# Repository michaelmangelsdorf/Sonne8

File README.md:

UPDATE: There is now a [successor project](https://github.com/michaelmangelsdorf/myth).

Computer project around an 8-bit microcontroller I've designed.

There are design files for a working single-board computer built around it in the 'Prototype' folder. I've had the PCB for it manufactured by JLCPCB during various revisions. The computer now works fine at 8 MHz system clock, which corresponds to around 1 million instructions per second. The main components are all 74HC-series CMOS chips. I basically wanted to design a CPU I could actually build from parts, not just inside an FPGA like [my previous](https://github.com/Dosflange/Paver) 16-bit machine.

The current reference schematics I'm using are [here](https://github.com/Dosflange/Myth/blob/main/docs/static/myth.pdf).
If I were to build another board, it would probably be based on the KiCad files in the 'Schematics' folder, where I
separated the schematics into functional modules.

So what this image shows is not an application board with an Arduino or anything, it is the actual microcontroller. The current version
has exactly 100 chips.

There are two software emulators I've written for this system. The code is very small, hopefully it's a good reference for finding out about the CPU.
The decoder-based [implementation](https://github.com/Dosflange/Myth/blob/main/Dev/src/clox/myth.h) is more high-level, and
the [dispatch table](https://github.com/Dosflange/Myth/blob/main/Dev/src/clox/vtable.c) version better suited to finding out about particular instructions.

[Documentation WIP](https://michaelmangelsdorf.github.io/Sonne8/)

__Update Sep.24__:

I've written a new assembler for this machine in Go(lang). The first thing I ported from the old format was
this multiplication routine. It multiplies two unsigned 8-bit numbers and returns a 16-bit result.
You can try it out with the tools in the 'Dev' folder.

```
Goldie/LOX assembly log
Page.Offset  Object code  Lid Line# Source text

                        048 0062  ;****** ***************************************************************
                        048 0063  P[Mul8]+  (Multiplies R by O, result in R and O)
                        048 0064  ;****** ***************************************************************
                        048 0065  
21.00:  07 5E           043 0066        OWN i6        (Save return pointer in L7/L6)
21.02:  79              043 0067        o1            (Multiplicand into L1, turns into low order result)
21.03:  68              043 0068        r0            (Multiplier into L0)
21.04:  10 6A           043 0069        CLR r2        (Clear high-order result, copy to L2)
21.06:  85 07           043 0070        ni 07h        (Initialise loop counter, 8 bits)
                        043 0071  
                        043 0072      O[Mul8Loop]
                        043 0073   
21.08:  80 01           043 0074        no 01h        (Bit mask for LSB)
21.0A:  61 18           043 0075        1r AND        (Check if multiplicand has LSB set)
21.0C:  8E 12           043 0076        nf >Mul8Skip  (Skip if not)
21.0E:  60 72 1B 6A     043 0077        0r 2o ADD r2  (Add multiplier to high order result)
                        043 0078  
                        043 0079      O[Mul8Skip]
                        043 0080  
21.12:  80 01           043 0081        no 01h        (Bit mask for LSB)
21.14:  62 18 6B        043 0082        2r AND r3     (Prepare flag of whether high order LSB is set)
21.17:  61 16 69        043 0083        1r SRR r1      (Shift low-order result right)
21.1A:  62 16 6A        043 0084        2r SRR r2       (Shift high-order result right)
                        043 0085  
21.1D:  63 8E 25        043 0086        3r nf >Mul8Done  (Check flag from earlier - HO LSB set?)
21.20:  84 80           043 0087        nr 80h          (Bit mask for MSB)
21.22:  71 19 69        043 0088        1o IOR r1     (Handle shift-result carry bit into MSB)
                        043 0089  
                        043 0090      O[Mul8Done]
                        043 0091  
21.25:  8C 08           043 0092        nw <Mul8Loop
21.27:  71              043 0093        1o            (Result low-order)
21.28:  62              043 0094        2r            (Result high-order)
21.29:  56 05           043 0095        6i RET        (Restore return pointer from L7/L6)
```

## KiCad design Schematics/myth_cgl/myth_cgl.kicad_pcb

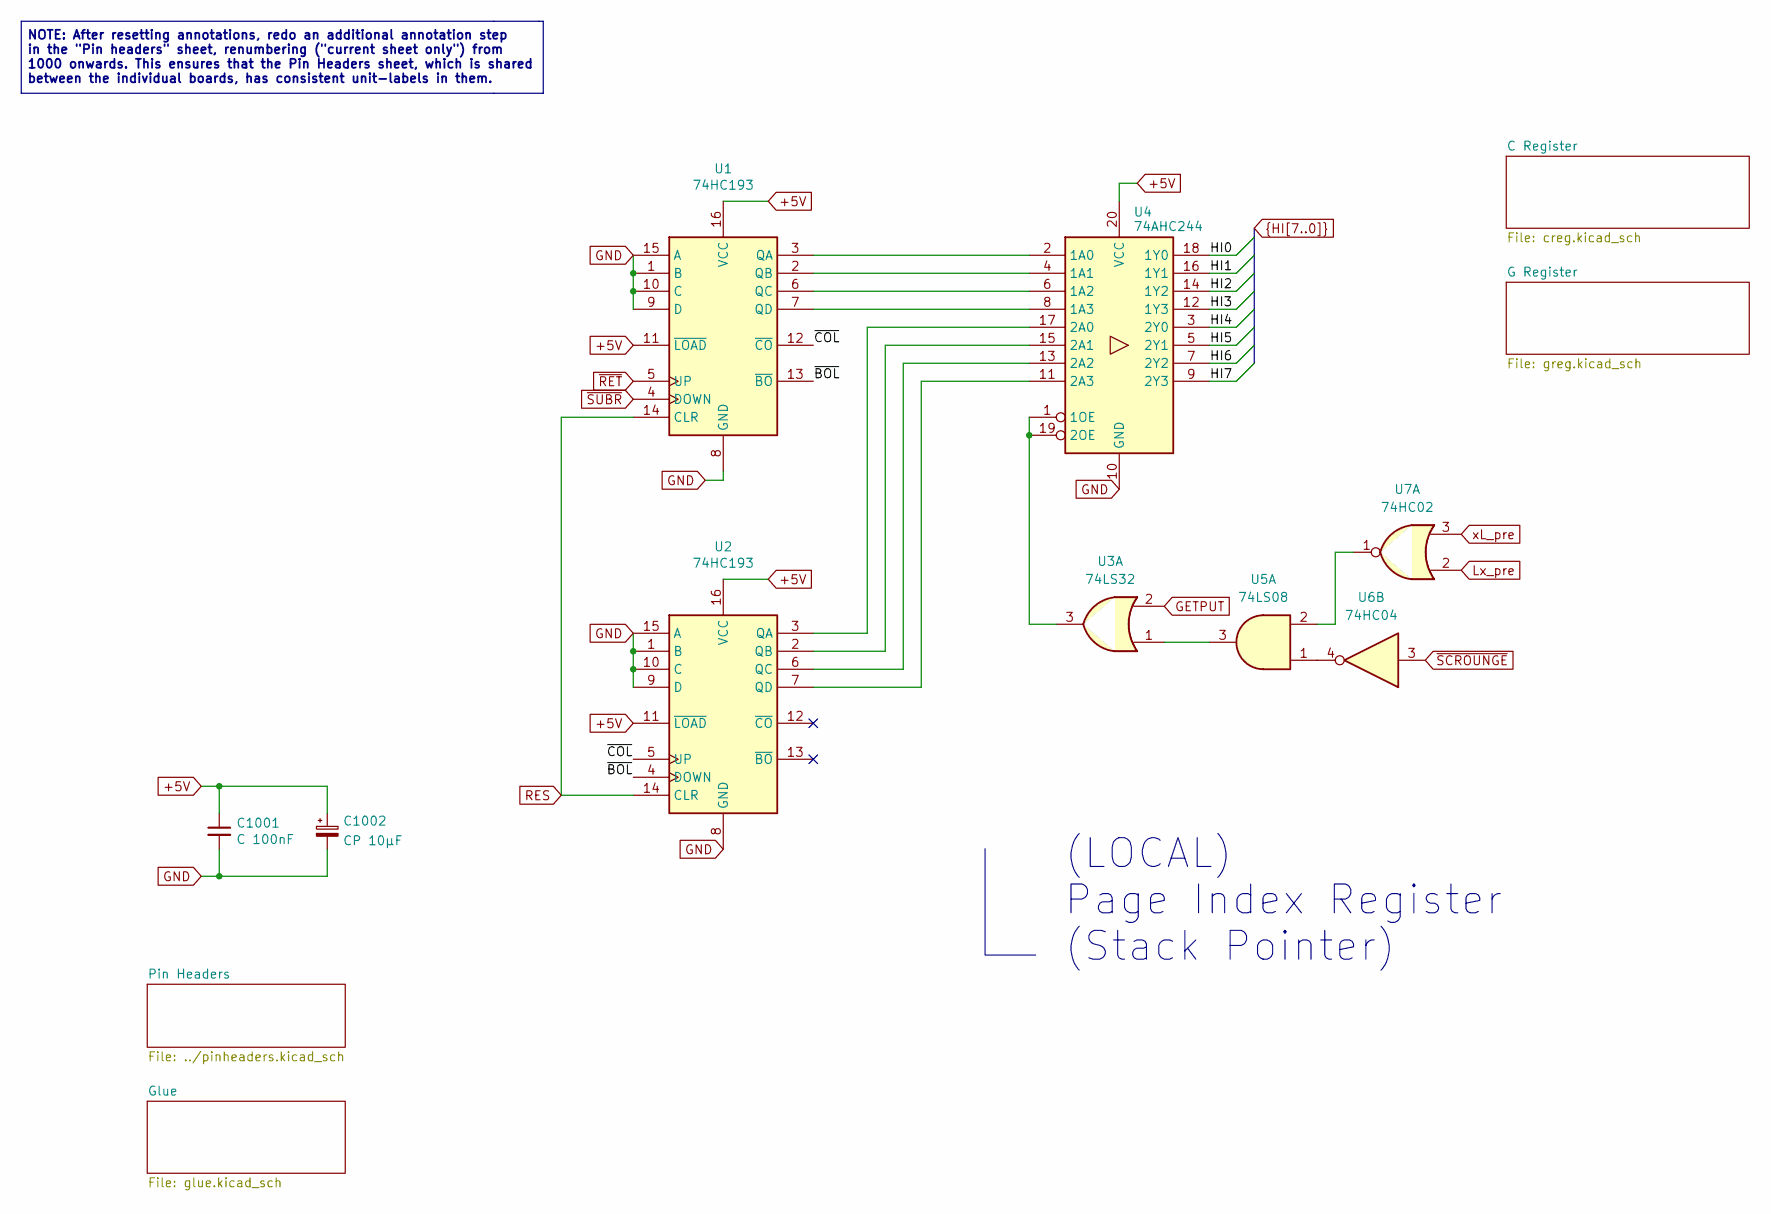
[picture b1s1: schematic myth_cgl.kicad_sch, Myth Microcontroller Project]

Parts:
C1001: C 100nF; C_Disc_D5.0mm_W2.5mm_P2.50mm
C1002: CP 10μF; CP_Radial_D6.3mm_P2.50mm
U1, U2: 74HC193; DIP-16_W7.62mm_Socket_LongPads
U3: 74LS32; DIP-14_W7.62mm_LongPads
U4: 74AHC244; DIP-20_W7.62mm_Socket_LongPads
U5: 74LS08; DIP-14_W7.62mm_LongPads
U6: 74HC04; DIP-14_W7.62mm_LongPads
U7: 74HC02; DIP-14_W7.62mm_LongPads

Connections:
+5V: C1001.1, C1002.1, U1.11 (~LOAD), U1.16 (VCC), U2.11 (~LOAD), U2.16 (VCC), U4.20 (VCC); also elsewhere on the board
/~BOL: U1.13 (~BO), U2.4 (DOWN)
/~COL: U1.12 (~CO), U2.5 (UP)
GETPUT: U3.2; also elsewhere on the board
HI0: U4.18 (1Y0); also elsewhere on the board
HI1: U4.16 (1Y1); also elsewhere on the board
HI2: U4.14 (1Y2); also elsewhere on the board
HI3: U4.12 (1Y3); also elsewhere on the board
HI4: U4.3 (2Y0); also elsewhere on the board
HI5: U4.5 (2Y1); also elsewhere on the board
HI6: U4.7 (2Y2); also elsewhere on the board
HI7: U4.9 (2Y3); also elsewhere on the board
Lx_pre: U7.2; also elsewhere on the board
unnamed: U1.3 (QA), U4.2 (1A0)
unnamed: U1.2 (QB), U4.4 (1A1)
unnamed: U1.6 (QC), U4.6 (1A2)
unnamed: U1.7 (QD), U4.8 (1A3)
unnamed: U2.3 (QA), U4.17 (2A0)
unnamed: U2.2 (QB), U4.15 (2A1)
unnamed: U2.6 (QC), U4.13 (2A2)
unnamed: U2.7 (QD), U4.11 (2A3)
unnamed: U3.1, U5.3
unnamed: U3.3, U4.1 (1OE), U4.19 (2OE)
unnamed: U5.1, U6.4
unnamed: U5.2, U7.1
RES: U1.14 (CLR), U2.14 (CLR); also elsewhere on the board
xL_pre: U7.3; also elsewhere on the board
~RET: U1.5 (UP); also elsewhere on the board
~SCROUNGE: U6.3
~SUBR: U1.4 (DOWN), U6.2; also elsewhere on the board

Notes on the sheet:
NOTE: After resetting annotations, redo an additional annotation step in the "Pin headers" sheet, renumbering ("current sheet only") from 1000 onwards. This ensures that the Pin Headers sheet, which is shared between the individual boards, has consistent unit-labels in them.
(LOCAL) Page Index Register (Stack Pointer)

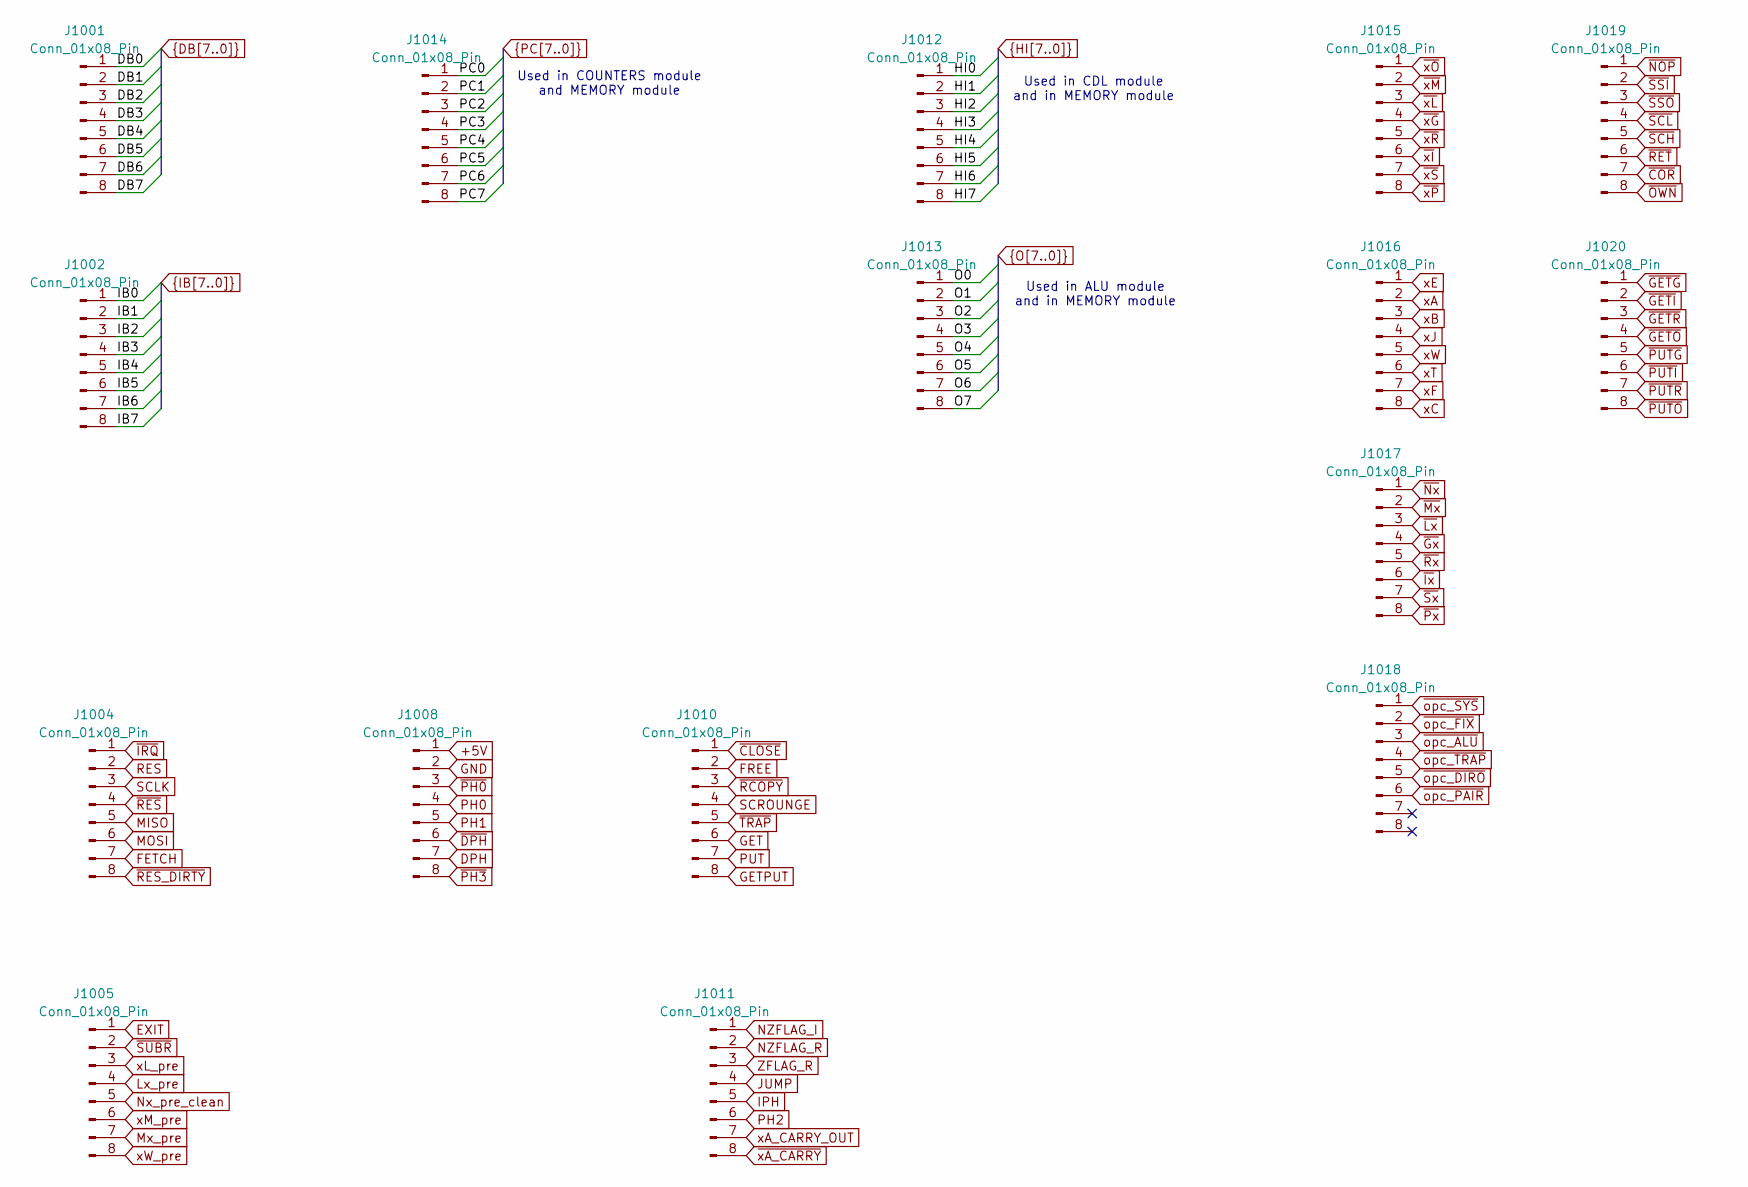
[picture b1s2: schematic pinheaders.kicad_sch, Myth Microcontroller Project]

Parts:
J1001, J1002, J1004, J1005, J1008, J1010, J1011, J1012, J1013, J1014, J1015, J1016, J1017, J1018, J1019, J1020: Conn_01x08_Pin; PinHeader_1x08_P2.54mm_Vertical

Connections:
+5V: J1008.1; also elsewhere on the board
DB0: J1001.1; also elsewhere on the board
DB1: J1001.2; also elsewhere on the board
DB2: J1001.3; also elsewhere on the board
DB3: J1001.4; also elsewhere on the board
DB4: J1001.5; also elsewhere on the board
DB5: J1001.6; also elsewhere on the board
DB6: J1001.7; also elsewhere on the board
DB7: J1001.8; also elsewhere on the board
DPH: J1008.7
EXIT: J1005.1; also elsewhere on the board
FETCH: J1004.7
FREE: J1010.2; also elsewhere on the board
GET: J1010.6
GETPUT: J1010.8; also elsewhere on the board
HI0: J1012.1; also elsewhere on the board
HI1: J1012.2; also elsewhere on the board
HI2: J1012.3; also elsewhere on the board
HI3: J1012.4; also elsewhere on the board
HI4: J1012.5; also elsewhere on the board
HI5: J1012.6; also elsewhere on the board
HI6: J1012.7; also elsewhere on the board
HI7: J1012.8; also elsewhere on the board
IB0: J1002.1
IB1: J1002.2
IB2: J1002.3
IB3: J1002.4
IB4: J1002.5
IB5: J1002.6
IB6: J1002.7
IB7: J1002.8
IPH: J1011.5; also elsewhere on the board
JUMP: J1011.4
Lx_pre: J1005.4; also elsewhere on the board
MISO: J1004.5
MOSI: J1004.6
Mx_pre: J1005.7; also elsewhere on the board
NZFLAG_I: J1011.1
NZFLAG_R: J1011.2
Nx_pre_clean: J1005.5; also elsewhere on the board
O0: J1013.1
O1: J1013.2
O2: J1013.3
O3: J1013.4
O4: J1013.5
O5: J1013.6
O6: J1013.7
O7: J1013.8
PC0: J1014.1
PC1: J1014.2
PC2: J1014.3
PC3: J1014.4
PC4: J1014.5
PC5: J1014.6
PC6: J1014.7
PC7: J1014.8
PH0: J1008.4
PH1: J1008.5
PH2: J1011.6
PUT: J1010.7
RES: J1004.2; also elsewhere on the board
SCLK: J1004.3
SCROUNGE: J1010.4
ZFLAG_R: J1011.3
xA: J1016.2
xA_CARRY_OUT: J1011.7
xB: J1016.3
xC: J1016.8; also elsewhere on the board
xE: J1016.1
xF: J1016.7
xJ: J1016.4
xL_pre: J1005.3; also elsewhere on the board
xM_pre: J1005.6; also elsewhere on the board
xT: J1016.6
xW: J1016.5
xW_pre: J1005.8
~CLOSE: J1010.1
~COR: J1019.7; also elsewhere on the board
~DPH: J1008.6
~Dx: J1017.4; also elsewhere on the board
~GETD: J1020.1
~GETI: J1020.2
~GETO: J1020.4
~GETR: J1020.3
~IRQ: J1004.1
~Ix: J1017.6
~Lx: J1017.3
~Mx: J1017.2
~NOP: J1019.1
~Nx: J1017.1
~OWN: J1019.8; also elsewhere on the board
~PH0: J1008.3; also elsewhere on the board
~PH3: J1008.8
~PUTD: J1020.5; also elsewhere on the board
~PUTI: J1020.6
~PUTO: J1020.8
~PUTR: J1020.7
~Px: J1017.8
~RCOPY: J1010.3
~RES_DIRTY: J1004.8
~RES: J1004.4; also elsewhere on the board
~RET: J1019.6; also elsewhere on the board
~Rx: J1017.5
~SCH: J1019.5
~SCL: J1019.4
~SSI: J1019.2
~SSO: J1019.3
~SUBR: J1005.2; also elsewhere on the board
~Sx: J1017.7
~TRAP: J1010.5
~opc_ALU: J1018.3
~opc_DIRO: J1018.5
~opc_FIX: J1018.2
~opc_PAIR: J1018.6
~opc_SYS: J1018.1
~opc_TRAP: J1018.4
~xA_CARRY: J1011.8; also elsewhere on the board
~xD: J1015.4
~xI: J1015.6
~xL: J1015.3
~xM: J1015.2
~xO: J1015.1
~xP: J1015.8
~xR: J1015.5
~xS: J1015.7

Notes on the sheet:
Used in COUNTERS module and MEMORY module
Used in CDL module and in MEMORY module
Used in ALU module and in MEMORY module

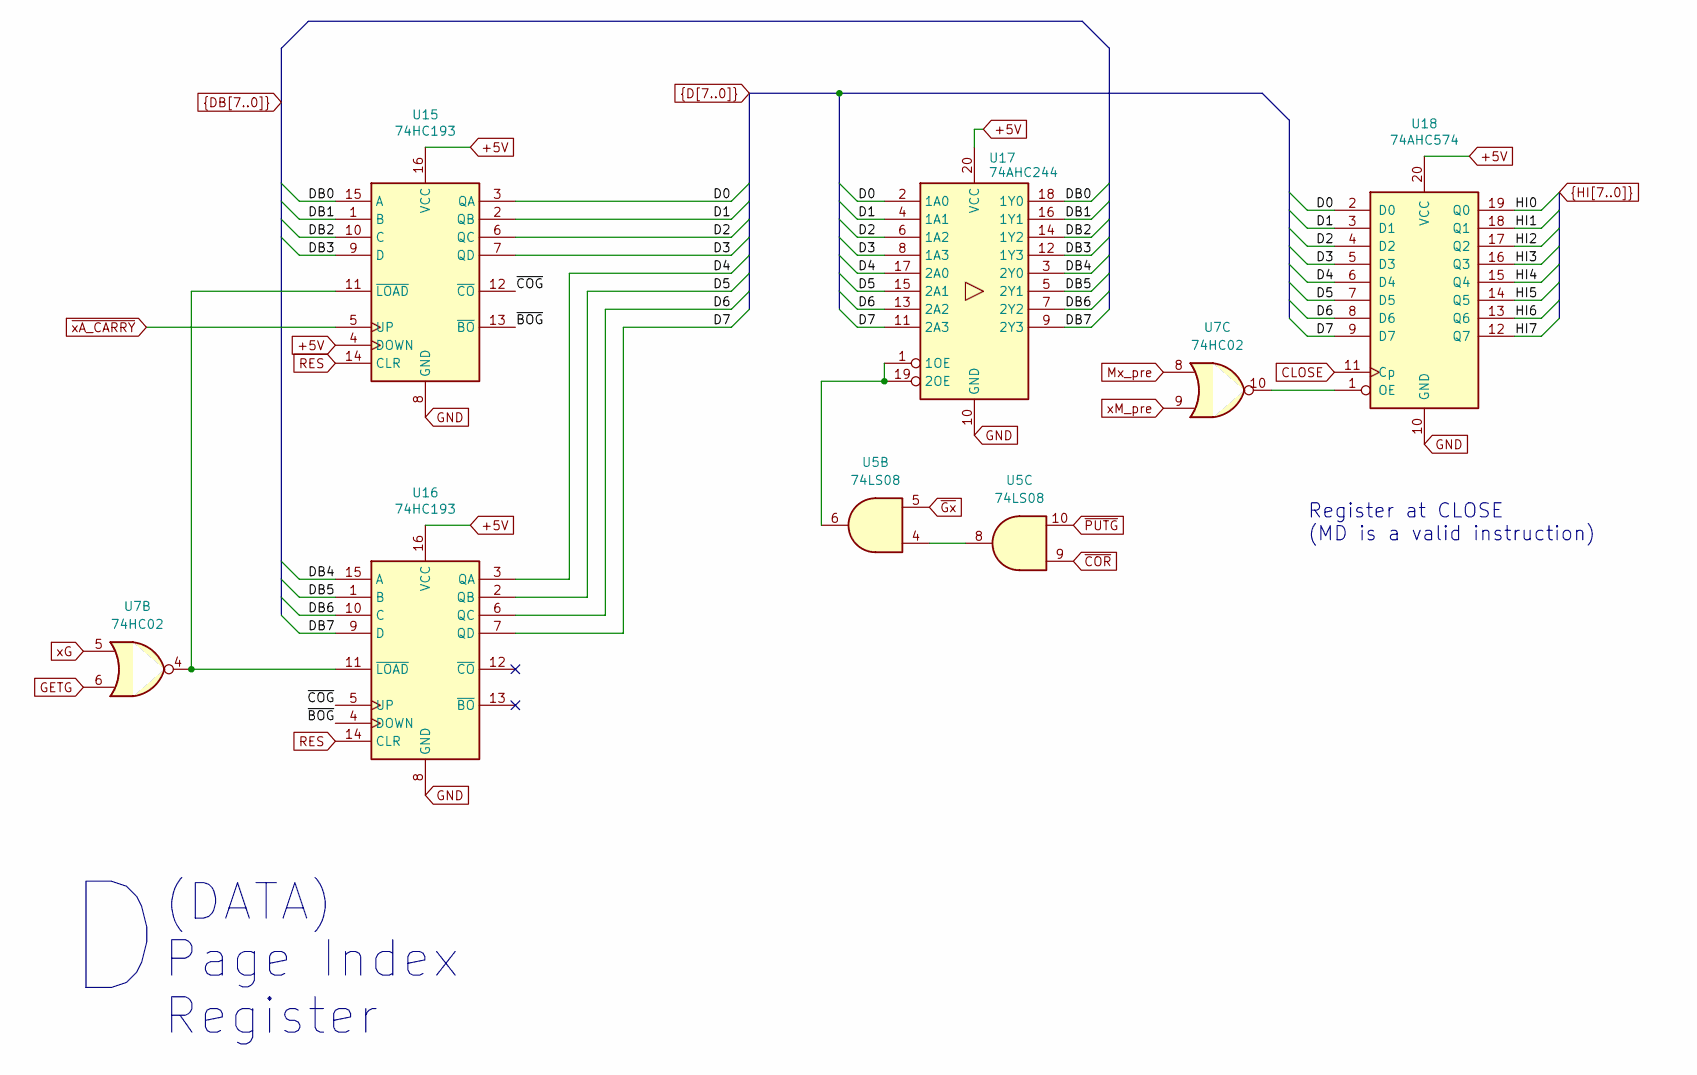
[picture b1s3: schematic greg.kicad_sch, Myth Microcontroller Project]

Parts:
U5: 74LS08; DIP-14_W7.62mm_LongPads
U7: 74HC02; DIP-14_W7.62mm_LongPads
U15, U16: 74HC193; DIP-16_W7.62mm_Socket_LongPads
U17: 74AHC244; DIP-20_W7.62mm_Socket_LongPads
U18: 74AHC574; DIP-20_W7.62mm_Socket_LongPads

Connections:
+5V: U15.4 (DOWN), U15.16 (VCC), U16.16 (VCC), U17.20 (VCC), U18.20 (VCC); also elsewhere on the board
/D Register/~BOD: U15.13 (~BO), U16.4 (DOWN)
/D Register/~COD: U15.12 (~CO), U16.5 (UP)
CLOSE: U18.11 (Cp); also elsewhere on the board
D0: U15.3 (QA), U17.2 (1A0), U18.2 (D0)
D1: U15.2 (QB), U17.4 (1A1), U18.3 (D1)
D2: U15.6 (QC), U17.6 (1A2), U18.4 (D2)
D3: U15.7 (QD), U17.8 (1A3), U18.5 (D3)
D4: U16.3 (QA), U17.17 (2A0), U18.6 (D4)
D5: U16.2 (QB), U17.15 (2A1), U18.7 (D5)
D6: U16.6 (QC), U17.13 (2A2), U18.8 (D6)
D7: U16.7 (QD), U17.11 (2A3), U18.9 (D7)
DB0: U15.15 (A), U17.18 (1Y0); also elsewhere on the board
DB1: U15.1 (B), U17.16 (1Y1); also elsewhere on the board
DB2: U15.10 (C), U17.14 (1Y2); also elsewhere on the board
DB3: U15.9 (D), U17.12 (1Y3); also elsewhere on the board
DB4: U16.15 (A), U17.3 (2Y0); also elsewhere on the board
DB5: U16.1 (B), U17.5 (2Y1); also elsewhere on the board
DB6: U16.10 (C), U17.7 (2Y2); also elsewhere on the board
DB7: U16.9 (D), U17.9 (2Y3); also elsewhere on the board
GETD: U7.6
HI0: U18.19 (Q0); also elsewhere on the board
HI1: U18.18 (Q1); also elsewhere on the board
HI2: U18.17 (Q2); also elsewhere on the board
HI3: U18.16 (Q3); also elsewhere on the board
HI4: U18.15 (Q4); also elsewhere on the board
HI5: U18.14 (Q5); also elsewhere on the board
HI6: U18.13 (Q6); also elsewhere on the board
HI7: U18.12 (Q7); also elsewhere on the board
Mx_pre: U7.8; also elsewhere on the board
unnamed: U5.4, U5.8
unnamed: U7.4, U15.11 (~LOAD), U16.11 (~LOAD)
unnamed: U5.6, U17.1 (1OE), U17.19 (2OE)
unnamed: U7.10, U18.1 (OE)
RES: U15.14 (CLR), U16.14 (CLR); also elsewhere on the board
xD: U7.5
xM_pre: U7.9; also elsewhere on the board
~COR: U5.9; also elsewhere on the board
~Dx: U5.5; also elsewhere on the board
~PUTD: U5.10; also elsewhere on the board
~xA_CARRY: U15.5 (UP); also elsewhere on the board

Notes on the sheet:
(DATA) Page Index Register
Register at CLOSE (MD is a valid instruction)

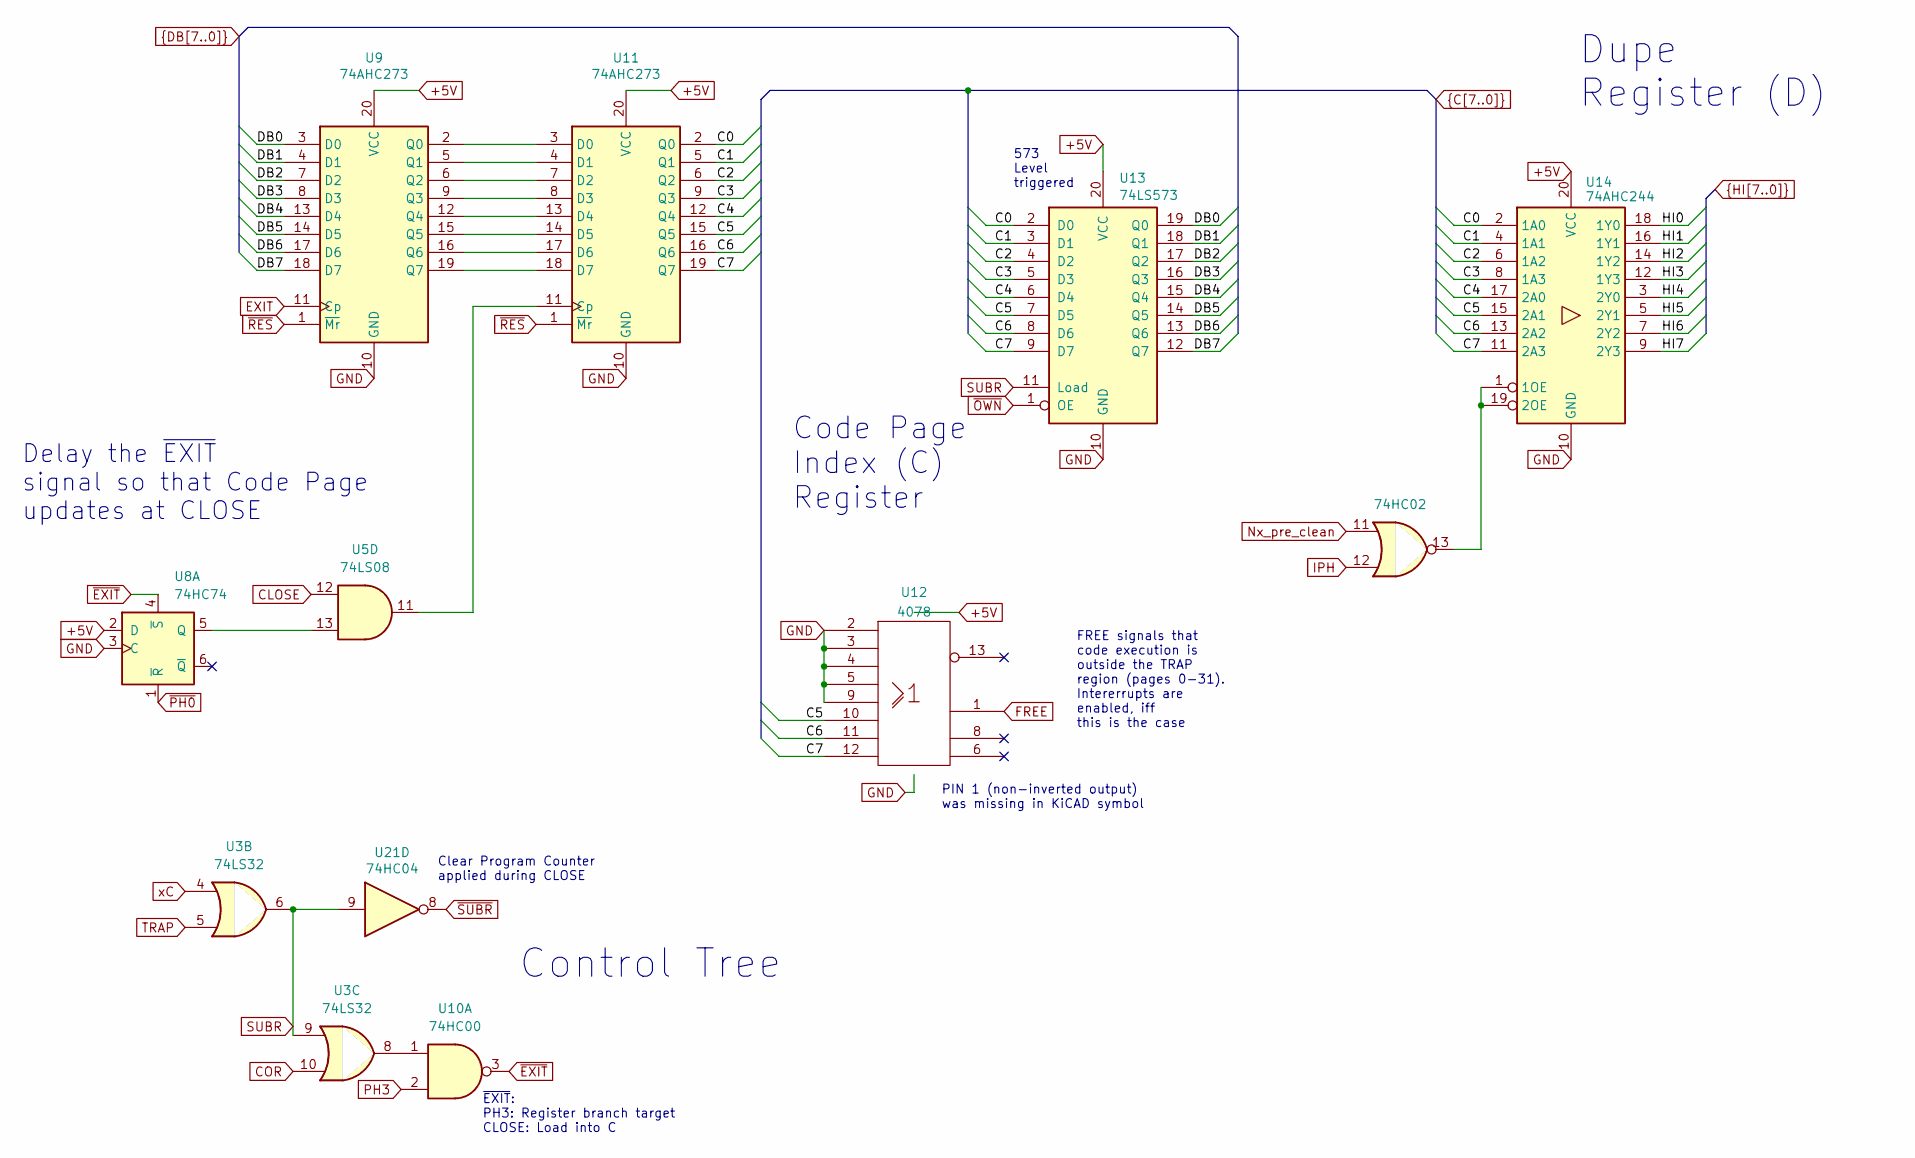
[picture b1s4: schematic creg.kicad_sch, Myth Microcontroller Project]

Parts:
U3: 74LS32; DIP-14_W7.62mm_LongPads
U5: 74LS08; DIP-14_W7.62mm_LongPads
U7: 74HC02; DIP-14_W7.62mm_LongPads
U8: 74HC74; DIP-14_W7.62mm_LongPads
U9, U11: 74AHC273; DIP-20_W7.62mm_Socket_LongPads
U10: 74HC00; DIP-14_W7.62mm_LongPads
U12: 4078; DIP-14_W7.62mm_Socket_LongPads
U13: 74LS573; DIP-20_W7.62mm_Socket_LongPads
U14: 74AHC244; DIP-20_W7.62mm_Socket_LongPads
U21: 74HC04; DIP-14_W7.62mm_LongPads

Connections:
+5V: U8.2 (D), U9.20 (VCC), U11.20 (VCC), U12.14 (Vdd), U13.20 (VCC), U14.20 (VCC); also elsewhere on the board
C0: U11.2 (Q0), U13.2 (D0), U14.2 (1A0)
C1: U11.5 (Q1), U13.3 (D1), U14.4 (1A1)
C2: U11.6 (Q2), U13.4 (D2), U14.6 (1A2)
C3: U11.9 (Q3), U13.5 (D3), U14.8 (1A3)
C4: U11.12 (Q4), U13.6 (D4), U14.17 (2A0)
C5: U11.15 (Q5), U12.10, U13.7 (D5), U14.15 (2A1)
C6: U11.16 (Q6), U12.11, U13.8 (D6), U14.13 (2A2)
C7: U11.19 (Q7), U12.12, U13.9 (D7), U14.11 (2A3)
CLOSE: U5.12; also elsewhere on the board
COR: U3.10
DB0: U9.3 (D0), U13.19 (Q0); also elsewhere on the board
DB1: U9.4 (D1), U13.18 (Q1); also elsewhere on the board
DB2: U9.7 (D2), U13.17 (Q2); also elsewhere on the board
DB3: U9.8 (D3), U13.16 (Q3); also elsewhere on the board
DB4: U9.13 (D4), U13.15 (Q4); also elsewhere on the board
DB5: U9.14 (D5), U13.14 (Q5); also elsewhere on the board
DB6: U9.17 (D6), U13.13 (Q6); also elsewhere on the board
DB7: U9.18 (D7), U13.12 (Q7); also elsewhere on the board
EXIT: U9.11 (Cp); also elsewhere on the board
FREE: U12.1; also elsewhere on the board
HI0: U14.18 (1Y0); also elsewhere on the board
HI1: U14.16 (1Y1); also elsewhere on the board
HI2: U14.14 (1Y2); also elsewhere on the board
HI3: U14.12 (1Y3); also elsewhere on the board
HI4: U14.3 (2Y0); also elsewhere on the board
HI5: U14.5 (2Y1); also elsewhere on the board
HI6: U14.7 (2Y2); also elsewhere on the board
HI7: U14.9 (2Y3); also elsewhere on the board
IPH: U7.12; also elsewhere on the board
unnamed: U5.13, U8.5 (Q)
unnamed: U3.8, U10.1
unnamed: U5.11, U11.11 (Cp)
unnamed: U9.2 (Q0), U11.3 (D0)
unnamed: U9.5 (Q1), U11.4 (D1)
unnamed: U9.6 (Q2), U11.7 (D2)
unnamed: U9.9 (Q3), U11.8 (D3)
unnamed: U9.12 (Q4), U11.13 (D4)
unnamed: U9.15 (Q5), U11.14 (D5)
unnamed: U9.16 (Q6), U11.17 (D6)
unnamed: U9.19 (Q7), U11.18 (D7)
unnamed: U7.13, U14.1 (1OE), U14.19 (2OE)
Nx_pre_clean: U7.11; also elsewhere on the board
PH3: U10.2
TRAP: U3.5
xC: U3.4; also elsewhere on the board
~EXIT: U8.4 (~S), U10.3
~OWN: U13.1 (OE); also elsewhere on the board
~PH0: U8.1 (~R); also elsewhere on the board
~RES: U9.1 (~Mr), U11.1 (~Mr); also elsewhere on the board

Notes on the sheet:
Code Page Index (C) Register
Clear Program Counter applied during CLOSE
PIN 1 (non-inverted output) was missing in KiCAD symbol
Dupe Register (D)
FREE signals that code execution is outside the TRAP region (pages 0-31). Intererrupts are enabled, iff this is the case
573 Level triggered
~{EXIT}: PH3: Register branch target CLOSE: Load into C
Delay the ~{EXIT} signal so that Code Page updates at CLOSE
Control Tree

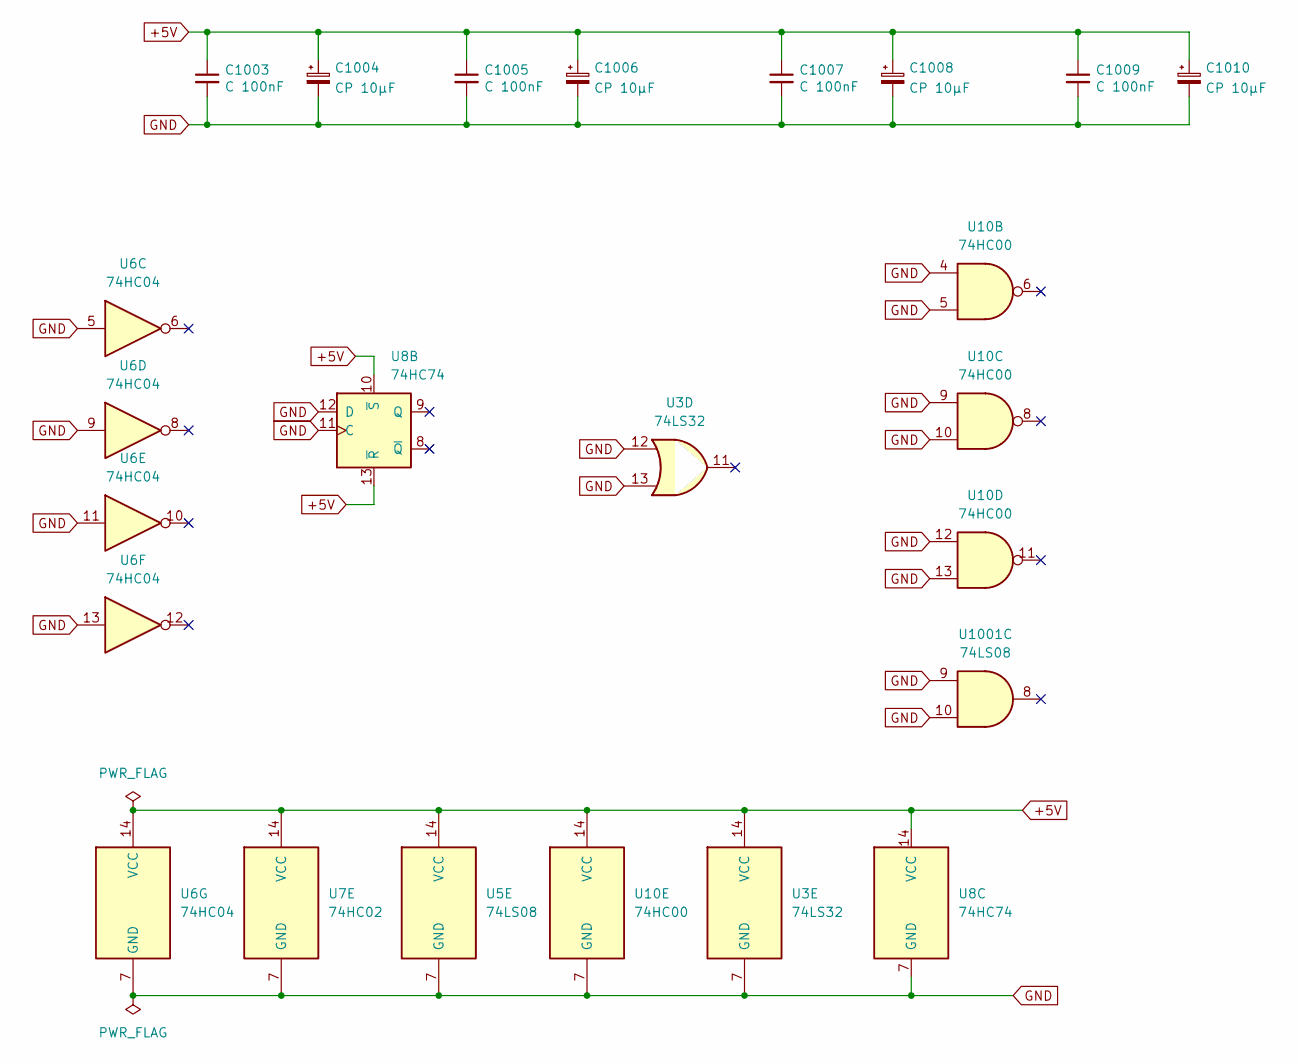
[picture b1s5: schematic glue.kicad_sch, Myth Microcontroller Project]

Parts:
C1003, C1005, C1007, C1009: C 100nF; C_Disc_D5.0mm_W2.5mm_P2.50mm
C1004, C1006, C1008, C1010: CP 10μF; CP_Radial_D6.3mm_P2.50mm
U3: 74LS32; DIP-14_W7.62mm_LongPads
U5, U1001: 74LS08; DIP-14_W7.62mm_LongPads
U6: 74HC04; DIP-14_W7.62mm_LongPads
U7: 74HC02; DIP-14_W7.62mm_LongPads
U8: 74HC74; DIP-14_W7.62mm_LongPads
U10: 74HC00; DIP-14_W7.62mm_LongPads

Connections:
+5V: C1003.1, C1004.1, C1005.1, C1006.1, C1007.1, C1008.1, C1009.1, C1010.1, U3.14 (VCC), U5.14 (VCC), U6.14 (VCC), U7.14 (VCC), U8.10 (~S), U8.13 (~R), U8.14 (VCC), U10.14 (VCC); also elsewhere on the board
~SUBR: U6.2; also elsewhere on the board

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
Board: 2 copper layers, 44 parts (0 on the bottom side), 89 nets, no tracks yet.

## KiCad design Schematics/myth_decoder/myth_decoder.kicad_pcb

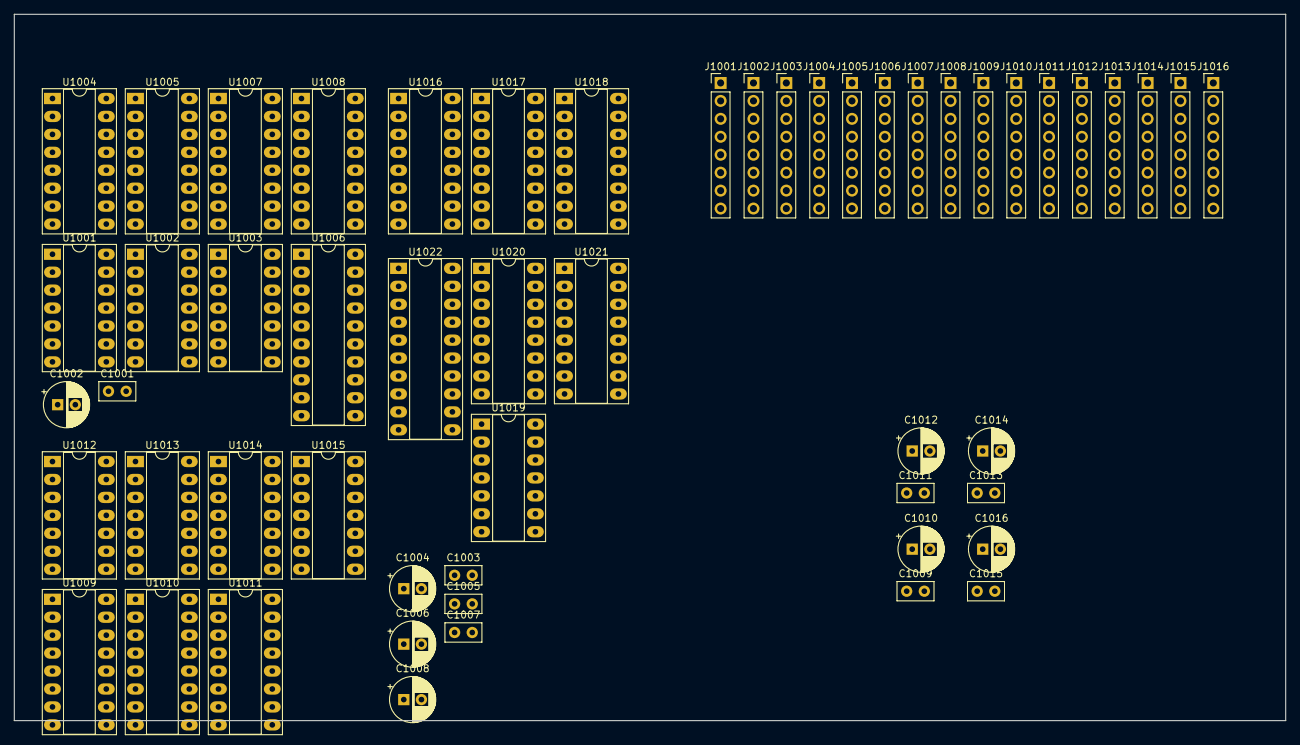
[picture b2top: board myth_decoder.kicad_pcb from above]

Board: 2 copper layers, 180.0 x 100.0 mm, 54 parts (0 on the bottom side), 107 nets, no tracks yet.

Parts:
C1001, C1003, C1005, C1007, C1009, C1011, C1013, C1015: C 100nF; C_Disc_D5.0mm_W2.5mm_P2.50mm
C1002, C1004, C1006, C1008, C1010, C1012, C1014, C1016: CP 10μF; CP_Radial_D6.3mm_P2.50mm
J1001, J1002, J1003, J1004, J1005, J1006, J1007, J1008, J1009, J1010, J1011, J1012, J1013, J1014, J1015, J1016: Conn_01x08_Pin; PinHeader_1x08_P2.54mm_Vertical
U1001: 74HC74; DIP-14_W7.62mm_Socket_LongPads
U1002, U1012: 74LS08; DIP-14_W7.62mm_Socket_LongPads
U1003: 74LS32; DIP-14_W7.62mm_Socket_LongPads
U1004, U1005: 74HC157; DIP-16_W7.62mm_Socket_LongPads
U1006: 74AHC273; DIP-20_W7.62mm_Socket_LongPads
U1007: 74LS148; DIP-16_W7.62mm_Socket_LongPads
U1008, U1016, U1018, U1020, U1021: 74AHC138; DIP-16_W7.62mm_Socket_LongPads
U1009, U1010, U1011, U1017: 74HC238; DIP-16_W7.62mm_Socket_LongPads
U1013: 74AHC04; DIP-14_W7.62mm_Socket_LongPads
U1014: 4078; DIP-14_W7.62mm_Socket_LongPads
U1015: 4075; DIP-14_W7.62mm_Socket_LongPads
U1019: 74HC02; DIP-14_W7.62mm_Socket_LongPads
U1022: 74AHC244; DIP-20_W7.62mm_Socket_LongPads

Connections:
+5V: C1001.1, C1002.1, C1003.1, C1004.1, C1005.1, C1006.1, C1007.1, C1008.1, C1009.1, C1010.1, C1011.1, C1012.1, C1013.1, C1014.1, C1015.1, C1016.1, J1005.1, U1001.2 (D), U1001.10 (~S), U1001.13 (~R), U1001.14 (VCC), U1002.14 (VCC), U1003.14 (VCC), U1004.16 (VCC), U1005.6 (I1b), U1005.16 (VCC), U1006.20 (VCC), U1007.16 (VCC), U1008.16 (VCC), U1009.6 (E3), U1009.16 (VCC), U1010.16 (VCC), U1011.6 (E3), U1011.16 (VCC), U1012.14 (VCC), U1013.14 (VCC), U1014.14 (Vdd), U1015.14 (VDD), U1016.16 (VCC), U1017.16 (VCC), U1018.6 (E3), U1018.16 (VCC), U1019.14 (VCC), U1020.6 (E3), U1020.16 (VCC), U1021.16 (VCC), U1022.20 (VCC)
/IW0: U1004.4 (Za), U1006.3 (D0)
/IW1: U1004.7 (Zb), U1006.4 (D1)
/IW2: U1004.9 (Zc), U1006.7 (D2)
/IW3: U1004.12 (Zd), U1006.8 (D3)
/IW4: U1005.4 (Za), U1006.13 (D4)
/IW5: U1005.7 (Zb), U1006.14 (D5)
/IW6: U1005.9 (Zc), U1006.17 (D6)
/IW7: U1005.12 (Zd), U1006.18 (D7)
DB0: J1001.1, U1004.2 (I0a), U1022.18 (1Y0)
DB1: J1001.2, U1004.5 (I0b), U1022.16 (1Y1)
DB2: J1001.3, U1004.11 (I0c), U1022.14 (1Y2)
DB3: J1001.4, U1004.14 (I0d), U1022.12 (1Y3)
DB4: J1001.5, U1005.2 (I0a), U1022.3 (2Y0)
DB5: J1001.6, U1005.5 (I0b), U1022.5 (2Y1)
DB6: J1001.7, U1005.11 (I0c), U1022.7 (2Y2)
DB7: J1001.8, U1005.14 (I0d), U1022.9 (2Y3)
DPH: J1005.7, U1016.6 (E3)
FREE: J1007.2, U1002.2
GET: J1007.6, U1002.8
GETPUT: J1007.8, U1002.5, U1002.9, U1019.1, U1021.6 (E3)
GND: C1001.2, C1002.2, C1003.2, C1004.2, C1005.2, C1006.2, C1007.2, C1008.2, C1009.2, C1010.2, C1011.2, C1012.2, C1013.2, C1014.2, C1015.2, C1016.2, J1005.2, U1001.3 (C), U1001.7 (GND), U1001.11 (C), U1001.12 (D), U1002.7 (GND), U1002.12, U1002.13, U1003.7 (GND), U1004.3 (I1a), U1004.6 (I1b), U1004.8 (GND), U1004.10 (I1c), U1004.13 (I1d), U1004.15 (E), U1005.3 (I1a), U1005.8 (GND), U1005.10 (I1c), U1005.13 (I1d), U1005.15 (E), U1006.10 (GND), U1007.2 (I5), U1007.3 (I6), U1007.4 (I7), U1007.8 (GND), U1008.4 (E1), U1008.8 (GND), U1009.8 (GND), U1010.5 (~E2), U1010.8 (GND), U1011.8 (GND), U1012.7 (GND), U1013.5, U1013.7 (GND), U1013.9, U1013.11, U1013.13, U1014.4, U1014.5, U1014.7 (Vss), U1014.9, U1014.10, U1014.11, U1014.12, U1015.3, U1015.4, U1015.5, U1015.7 (VSS), U1015.11, U1015.12, U1015.13, U1016.8 (GND), U1017.4 (~G2A), U1017.8 (GND), U1018.8 (GND), U1019.5, U1019.6, U1019.7 (GND), U1019.8, U1019.9, U1019.11, U1019.12, U1020.5 (E2), U1020.8 (GND), U1021.4 (E1), U1021.5 (E2), U1021.8 (GND), U1022.10 (GND), U1022.11 (2A3), U1022.13 (2A2), U1022.15 (2A1)
IB0: J1002.1, U1006.2 (Q0), U1009.1 (A0), U1010.1 (A0), U1017.1 (A0), U1018.1 (A0), U1020.1 (A0), U1022.2 (1A0)
IB1: J1002.2, U1006.5 (Q1), U1009.2 (A1), U1010.2 (A1), U1017.2 (A1), U1018.2 (A1), U1020.2 (A1), U1022.4 (1A1)
IB2: J1002.3, U1006.6 (Q2), U1009.3 (A2), U1010.3 (A2), U1017.3 (A2), U1018.3 (A2), U1020.3 (A2), U1022.6 (1A2)
IB3: J1002.4, U1002.4, U1006.9 (Q3), U1007.10 (IO), U1009.5 (~E2), U1010.6 (E3), U1011.5 (~E2), U1013.3, U1017.6 (G1), U1018.4 (E1), U1021.3 (A2), U1022.8 (1A3)
IB4: J1002.5, U1006.12 (Q4), U1007.11 (I1), U1011.1 (A0), U1016.1 (A0), U1021.1 (A0), U1022.17 (2A0)
IB5: J1002.6, U1006.15 (Q5), U1007.12 (I2), U1011.2 (A1), U1016.2 (A1), U1021.2 (A1)
IB6: J1002.7, U1006.16 (Q6), U1007.13 (I3), U1011.3 (A2), U1016.3 (A2)
IB7: J1002.8, U1006.19 (Q7), U1007.1 (I4)
Lx_pre: J1004.4, U1003.1, U1011.13 (Y2)
Mx_pre: J1004.7, U1003.2, U1011.14 (Y1)
unnamed: U1001.5 (Q), U1002.1
unnamed: U1001.4 (~S), U1003.8
unnamed: U1002.10, U1013.4
unnamed: U1003.3, U1012.1
unnamed: U1003.6, U1012.2, U1012.5
unnamed: U1002.3, U1004.1 (S), U1005.1 (S)
unnamed: U1007.14 (GS), U1008.6 (E3)
unnamed: U1007.9 (S0), U1008.1 (A0)
unnamed: U1007.7 (S1), U1008.2 (A1)
unnamed: U1007.6 (S2), U1008.3 (A2)
unnamed: U1012.3, U1014.2
unnamed: U1012.6, U1013.1, U1014.3
unnamed: U1012.9, U1013.2
Nx_pre: U1011.15 (Y0), U1012.4, U1012.10
Nx_pre_clean: J1004.5, U1012.8, U1012.13
PH0: J1005.4, U1008.5 (E2)
PH1: J1005.5, U1006.11 (Cp), U1012.12
PUT: J1007.7, U1002.6
SCROUNGE: J1007.4, U1014.1, U1015.8, U1016.5 (E2)
xA: J1012.2, U1017.14 (Y1)
xB: J1012.3, U1017.13 (Y2)
xC: J1012.8, U1017.7 (Y7)
xE: J1012.1, U1017.15 (Y0)
xF: J1012.7, U1017.9 (Y6)
xJ: J1012.4, U1017.12 (Y3)
xL_pre: J1004.3, U1003.4, U1009.13 (Y2)
xM_pre: J1004.6, U1003.5, U1009.14 (Y1)
xT: J1012.6, U1017.10 (Y5)
xW: J1012.5, U1017.11 (Y4)
xW_pre: J1004.8, U1010.11 (Y4)
~CLOSE: J1007.1, U1001.1 (~R)
~COR: J1015.7, U1020.9 (O6)
~DPH: J1005.6, U1003.13, U1019.3
~Dx: J1013.4, U1016.12 (O3)
~GETD: J1016.1, U1021.15 (O0)
~GETI: J1016.2, U1021.14 (O1)
~GETO: J1016.4, U1021.12 (O3)
~GETR: J1016.3, U1021.13 (O2)
~IRQ: J1003.1, U1003.9
~Ix: J1013.6, U1016.10 (O5)
~Lx: J1013.3, U1016.13 (O2)
~Mx: J1013.2, U1016.14 (O1)
~NOP: J1015.1, U1020.15 (O0)
~Nx: J1013.1, U1016.15 (O0)
~OWN: J1015.8, U1020.7 (O7)
~PH0: J1005.3, U1003.10, U1006.1 (~Mr), U1007.5 (EI)
~PH3: J1005.8, U1015.2
~PUTD: J1016.5, U1021.11 (O4)
~PUTI: J1016.6, U1021.10 (O5)
~PUTO: J1016.8, U1021.7 (O7)
~PUTR: J1016.7, U1021.9 (O6)
~Px: J1013.8, U1016.7 (O7)
~RCOPY: J1007.3, U1015.9, U1017.5 (~G2B), U1018.5 (E2)
~RET: J1015.6, U1020.10 (O5)
~Rx: J1013.5, U1016.11 (O4)
~SCH: J1015.5, U1020.11 (O4)
~SCL: J1015.4, U1020.12 (O3)
~SSI: J1015.2, U1020.14 (O1)
~SSO: J1015.3, U1020.13 (O2)
~Sx: J1013.7, U1016.9 (O6)
~TRAP: J1007.5, U1003.11, U1022.1 (1OE), U1022.19 (2OE)
~opc_ALU: J1014.3, U1008.14 (O1)
~opc_DIRO: J1014.5, U1008.12 (O3), U1019.2
~opc_FIX: J1014.2, U1008.15 (O0)
~opc_PAIR: J1014.6, U1008.11 (O4), U1009.4 (~E1), U1010.4 (~E1), U1011.4 (~E1), U1015.1, U1016.4 (E1)
~opc_SYS: J1014.1, U1007.15 (EO), U1020.4 (E1)
~opc_TRAP: J1014.4, U1003.12, U1008.13 (O2)
~xD: J1011.4, U1018.12 (O3)
~xI: J1011.6, U1018.10 (O5)
~xL: J1011.3, U1018.13 (O2)
~xM: J1011.2, U1018.14 (O1)
~xO: J1011.1, U1018.15 (O0)
~xP: J1011.8, U1018.7 (O7)
~xR: J1011.5, U1018.11 (O4)
~xS: J1011.7, U1018.9 (O6)
